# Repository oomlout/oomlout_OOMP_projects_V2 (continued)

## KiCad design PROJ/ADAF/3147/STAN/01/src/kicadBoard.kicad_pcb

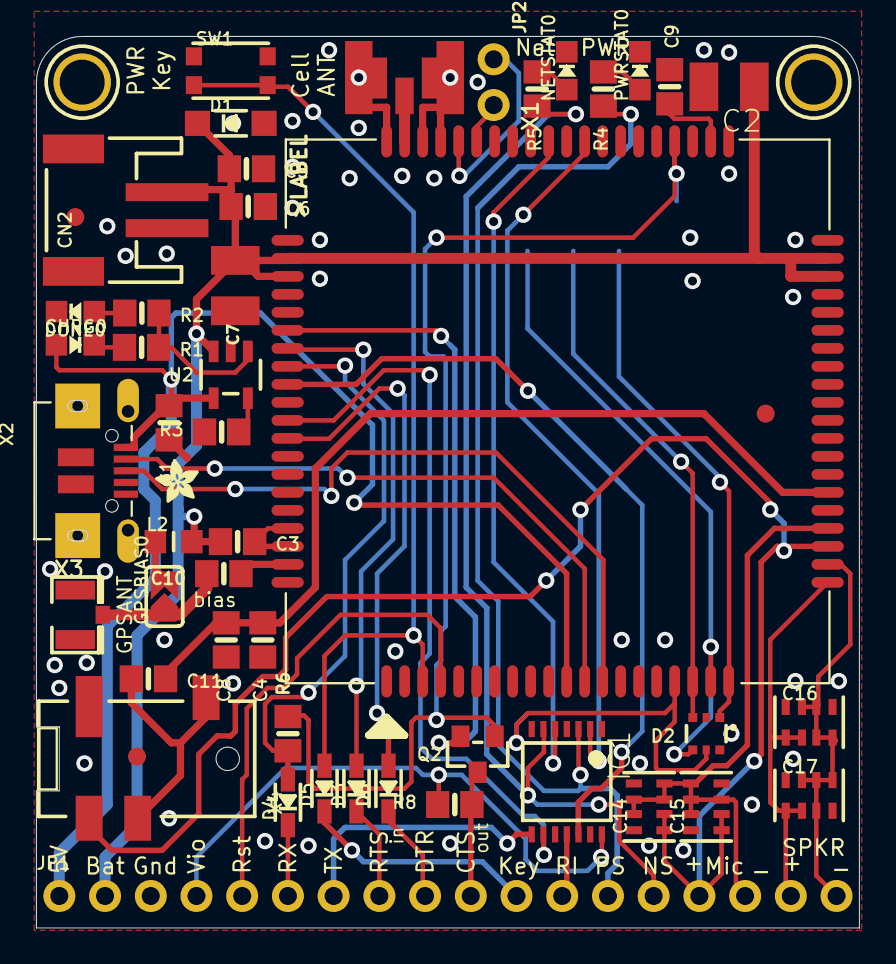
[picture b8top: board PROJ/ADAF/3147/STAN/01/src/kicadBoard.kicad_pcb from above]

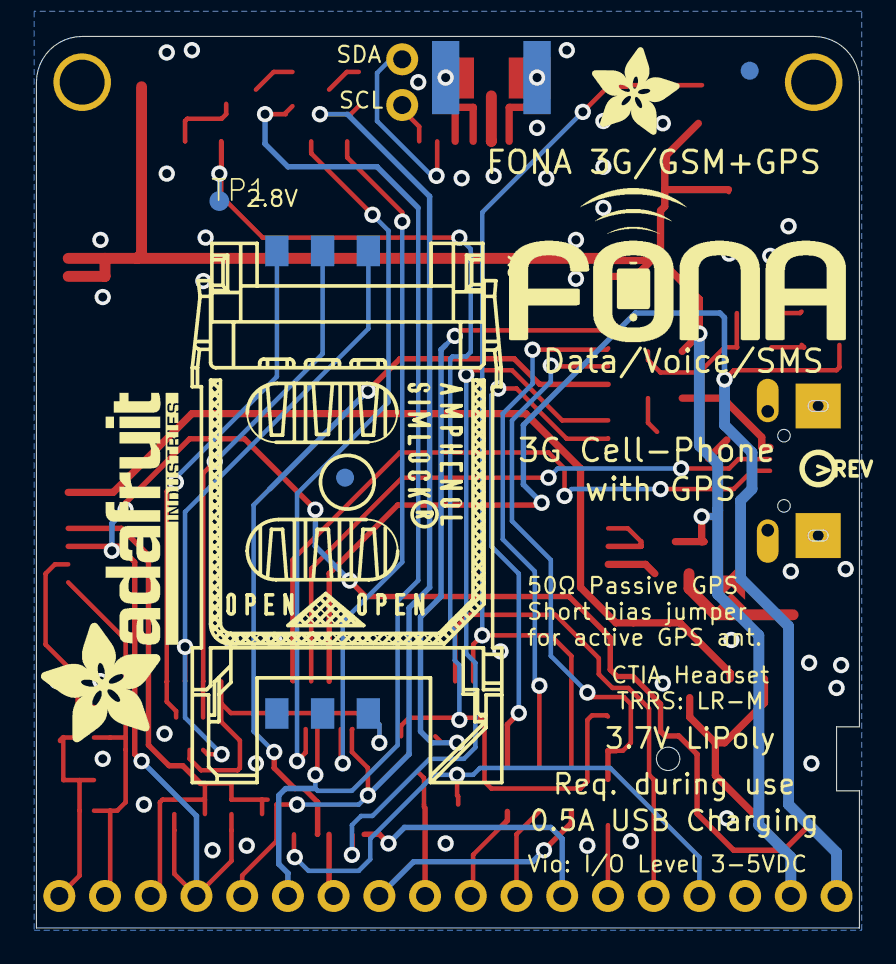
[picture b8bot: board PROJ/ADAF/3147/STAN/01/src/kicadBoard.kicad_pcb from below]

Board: 2 copper layers, 45.7 x 49.5 mm, 60 parts (8 on the bottom side), 49 nets.

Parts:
C1: 10µF; 0805-NO
C2, C7: 100uF; C1210
C3, C4, C6, C10: 33pF; 0805-NO
C5, C8: 10pF; 0805-NO
C9, C11: 10uF; 0805-NO
C14, C16: 33pF; RESPACK_4X0603
C15, C17: 10pF; RESPACK_4X0603
CHRG0: ORANGE; CHIPLED_0805_NOOUTLINE
CN2: JSTPH; JSTPH2
D1: MMSZ5231BT1G; SOD-123
D2: SMF05C; SOT363
D3, D4, D5, D6: 1N4148; SOD-323
DONE0: GREEN; CHIPLED_0805_NOOUTLINE
FID1, FID2, FID3, FID4, FID5: FIDUCIAL""; FIDUCIAL_1MM
GPSBIAS0: SOLDERJUMPER_ARROW_NOPASTE
IC1: 74VHCT125PW; TSSOP14
JP1: 1X18_ROUND70
JP2: 1X02_ROUND
L2: 33nH; _0805MP
NETSTAT0: RED; CHIPLED_0805_NOOUTLINE
PWRSTAT0: GREEN; CHIPLED_0805_NOOUTLINE
Q2: bss138; SOT23-WIDE
R1: 470; 0805-NO
R2, R4, R5: 1K; 0805-NO
R3, R6: 2K; 0805-NO
R8: 10K; 0805-NO
SW1: KMR2; BTN_KMR2_4.6X2.8
TP1: TPTP11R; TP11R
U1: SIM5320
U2: MCP73831T-2ACI/OT; SOT23-5
U$21: ADAFRUIT_2.5MM
U$25: PCBFEAT-REV-040
U$26: FONA_LOGO
U$33, U$34: MOUNTINGHOLE2.5; MOUNTINGHOLE_2.5_PLATED
U$36: ADAFRUIT_5MM
U$42: ADAFRUIT_TEXT_20MM
X1: uFL; SMA_EDGELAUNCH_UFL
X2: MicroB; 4UCONN_20329
X3: uFL; U.FL
X4: 4UCONN_18510
X6: SIM_LOCKAMPHENOL; C707_10M006_512_2

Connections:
1.8V: D2.1, U1.20, X6.C1
2.8V: Q2.1, R6.2, TP1.TP, U1.44
+5V: C1.1, CHRG0.A, JP1.1, U1.11, U2.4, X2.VBUS
CTS_5V: D3.C, JP1.8
DM: U1.12, X2.D-
DP: U1.13, X2.D+
DTR_5V: D6.C, JP1.9
EAR+: C4.1, C8.1, C11.2, U1.26
GND: C1.2, C2.2, C3.2, C4.2, C5.2, C6.2, C7.2, C8.2, C9.2, C14.5, C14.8, C15.4, C15.8, C16.5, C16.8, C17.4, C17.8, CN2.1, D1.A, D2.2, DONE0.C, IC1.1, IC1.4, IC1.7, IC1.10, IC1.13, JP1.3, NETSTAT0.C, PWRSTAT0.C, R3.2, SW1.A, SW1.A', U1.1, U1.2, U1.5, U1.10, U1.14, U1.37, U1.40, U1.41, U1.43, U1.57, U1.58, U1.60, U1.61, U1.64, U1.65, U1.77, U1.78, U1.80, U2.2, X1.GND@1, X1.GND@2, X1.GND@3, X1.GND@4, X2.BASE@1, X2.BASE@2, X2.GND, X2.SPRT@1, X2.SPRT@2, X2.SPRT@3, X2.SPRT@4, X3.1, X3.2, X4.4-INNER_SLEEVE, X6.C5
GSM_ANT: U1.59, X1.P
HP+: C11.1, X4.2-TIP, X4.3-OUTER_SLEEVE
I2C_SCL: JP2.2, U1.55
I2C_SDA: JP2.1, U1.56
MIC+: C14.1, C14.2, C15.1, C15.2, JP1.15, U1.23, X4.1-GND
MIC-: C14.3, C14.4, C14.6, C14.7, C15.3, C15.5, C15.6, C15.7, JP1.16, U1.24
unnamed: CHRG0.C, R1.1
unnamed: R1.2, R2.2, U2.1
unnamed: C10.2, GPSBIAS0.1, X3.3
unnamed: PWRSTAT0.A, R4.1
unnamed: R3.1, U2.5
unnamed: DONE0.A, R2.1
unnamed: C10.1, U1.79
unnamed: NETSTAT0.A, R5.1
unnamed: GPSBIAS0.2, L2.1
NETSTAT: IC1.5, U1.51
NETSTAT_5V: IC1.6, JP1.14, R5.2
PWRKEY: D5.A, SW1.B, SW1.B', U1.3
PWRKEY_5V: D5.C, JP1.11
PWRSTAT: IC1.2, U1.49
PWRSTAT_5V: IC1.3, JP1.13, R4.2
RESET_5V: JP1.5, U1.4
RI: IC1.12, U1.69
RI_5V: IC1.11, JP1.12
RTS_5V: JP1.10, Q2.3, R8.1
RXD_5V: D4.C, JP1.6
SIMCLK: D2.4, U1.19, X6.C3
SIMDATA: D2.5, U1.17, X6.C7
SIMRST: D2.3, U1.18, X6.C2
SPEAKER+: C16.1, C16.2, C17.1, C17.2, JP1.17, U1.21
SPEAKER-: C16.3, C16.4, C16.6, C16.7, C17.3, C17.5, C17.6, C17.7, JP1.18, U1.22
TXD_5V: IC1.8, JP1.7
UART_CTS: D3.A, U1.67
UART_DTR: D6.A, U1.72
UART_RTS: Q2.2, U1.66
UART_RXD: D4.A, R6.1, U1.68
UART_TXD: IC1.9, U1.71
VBAT: C2.1, C3.1, C5.1, C6.1, C7.1, CN2.2, D1.C, JP1.2, L2.2, U1.38, U1.39, U1.62, U1.63, U2.3
VCCIO: IC1.14, JP1.4, R8.2
VRTC: C9.1, U1.42
